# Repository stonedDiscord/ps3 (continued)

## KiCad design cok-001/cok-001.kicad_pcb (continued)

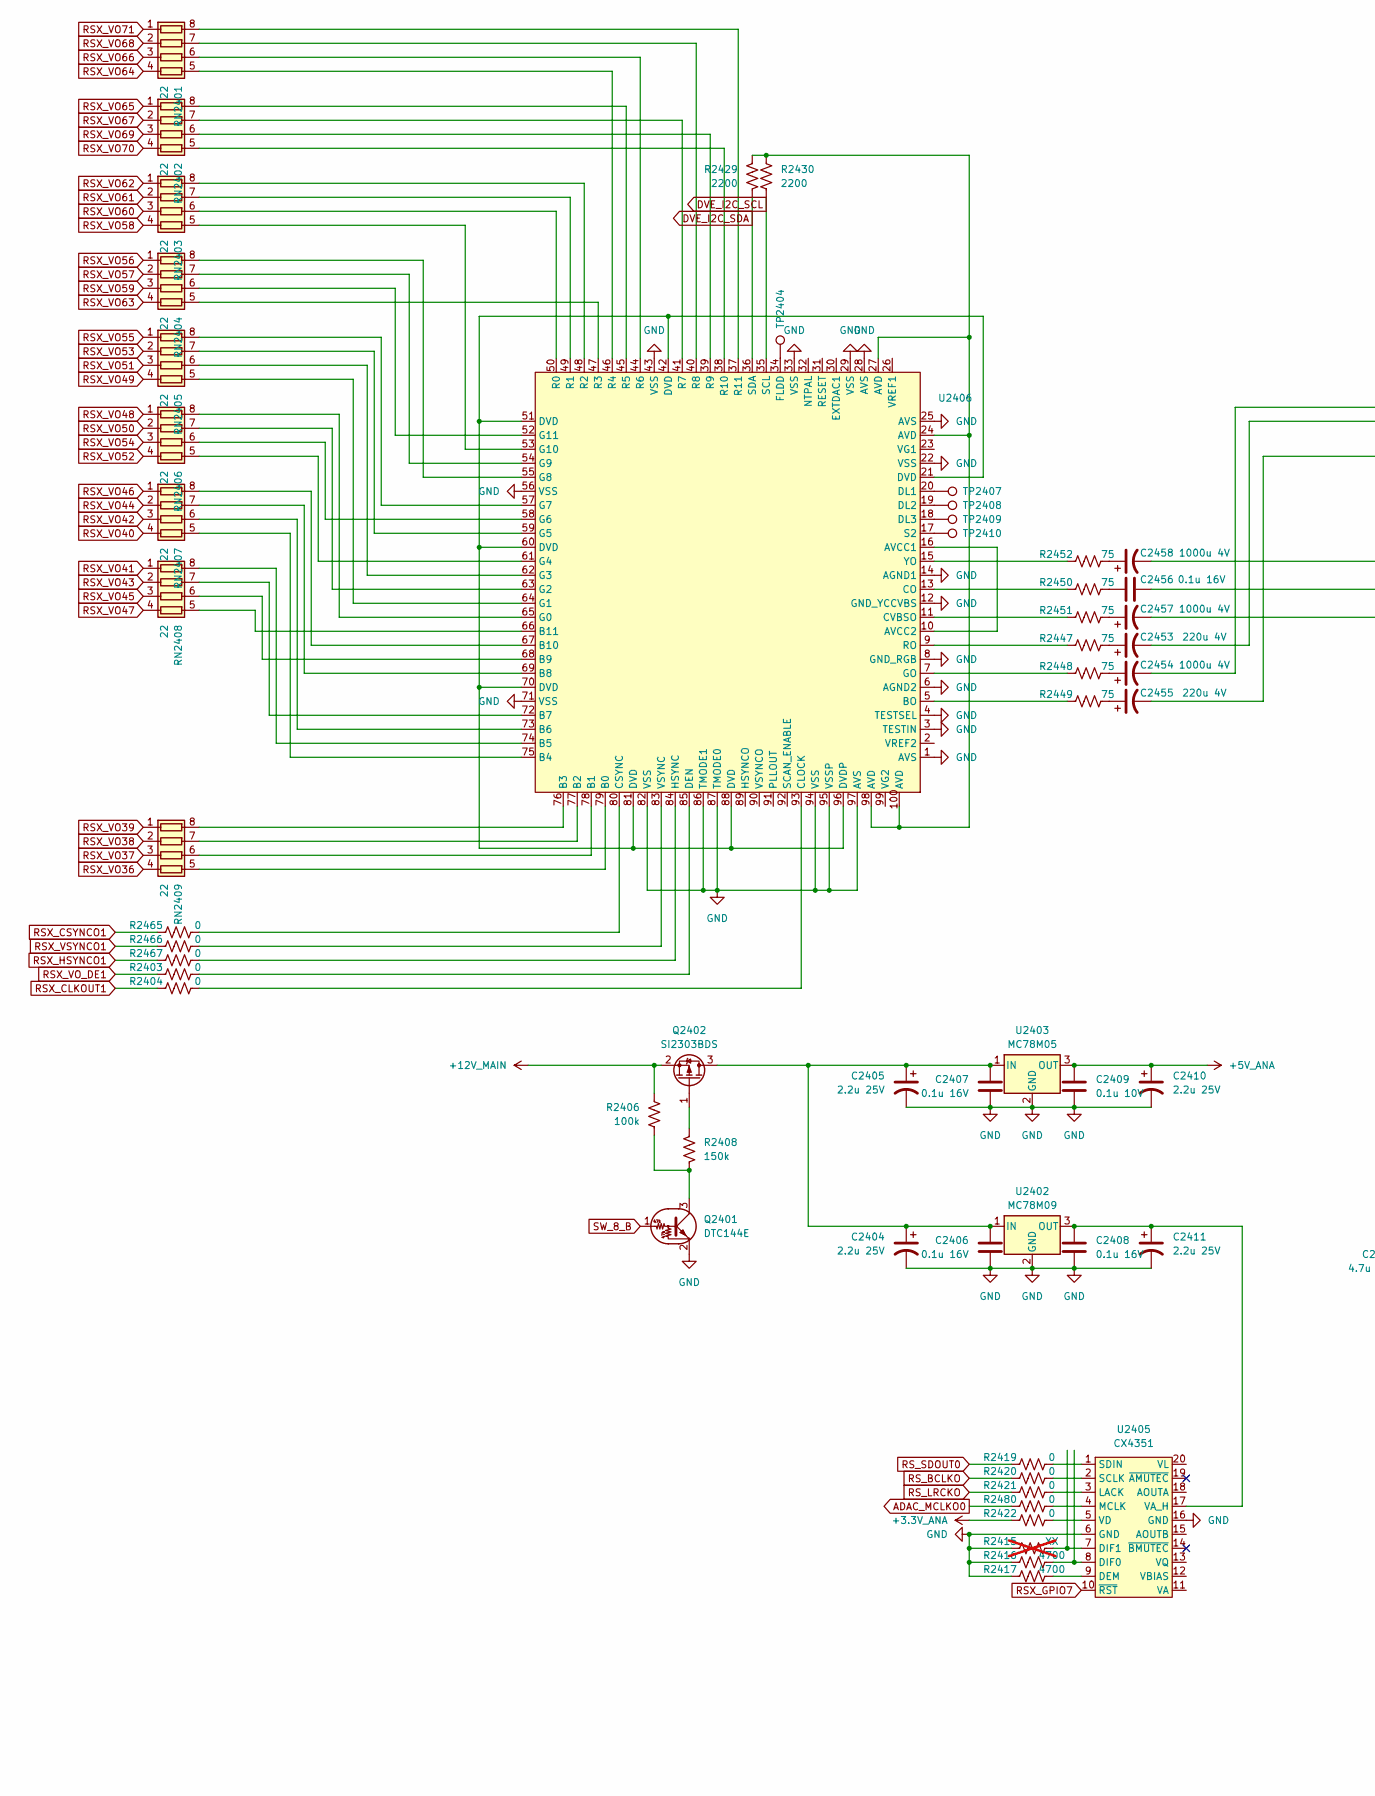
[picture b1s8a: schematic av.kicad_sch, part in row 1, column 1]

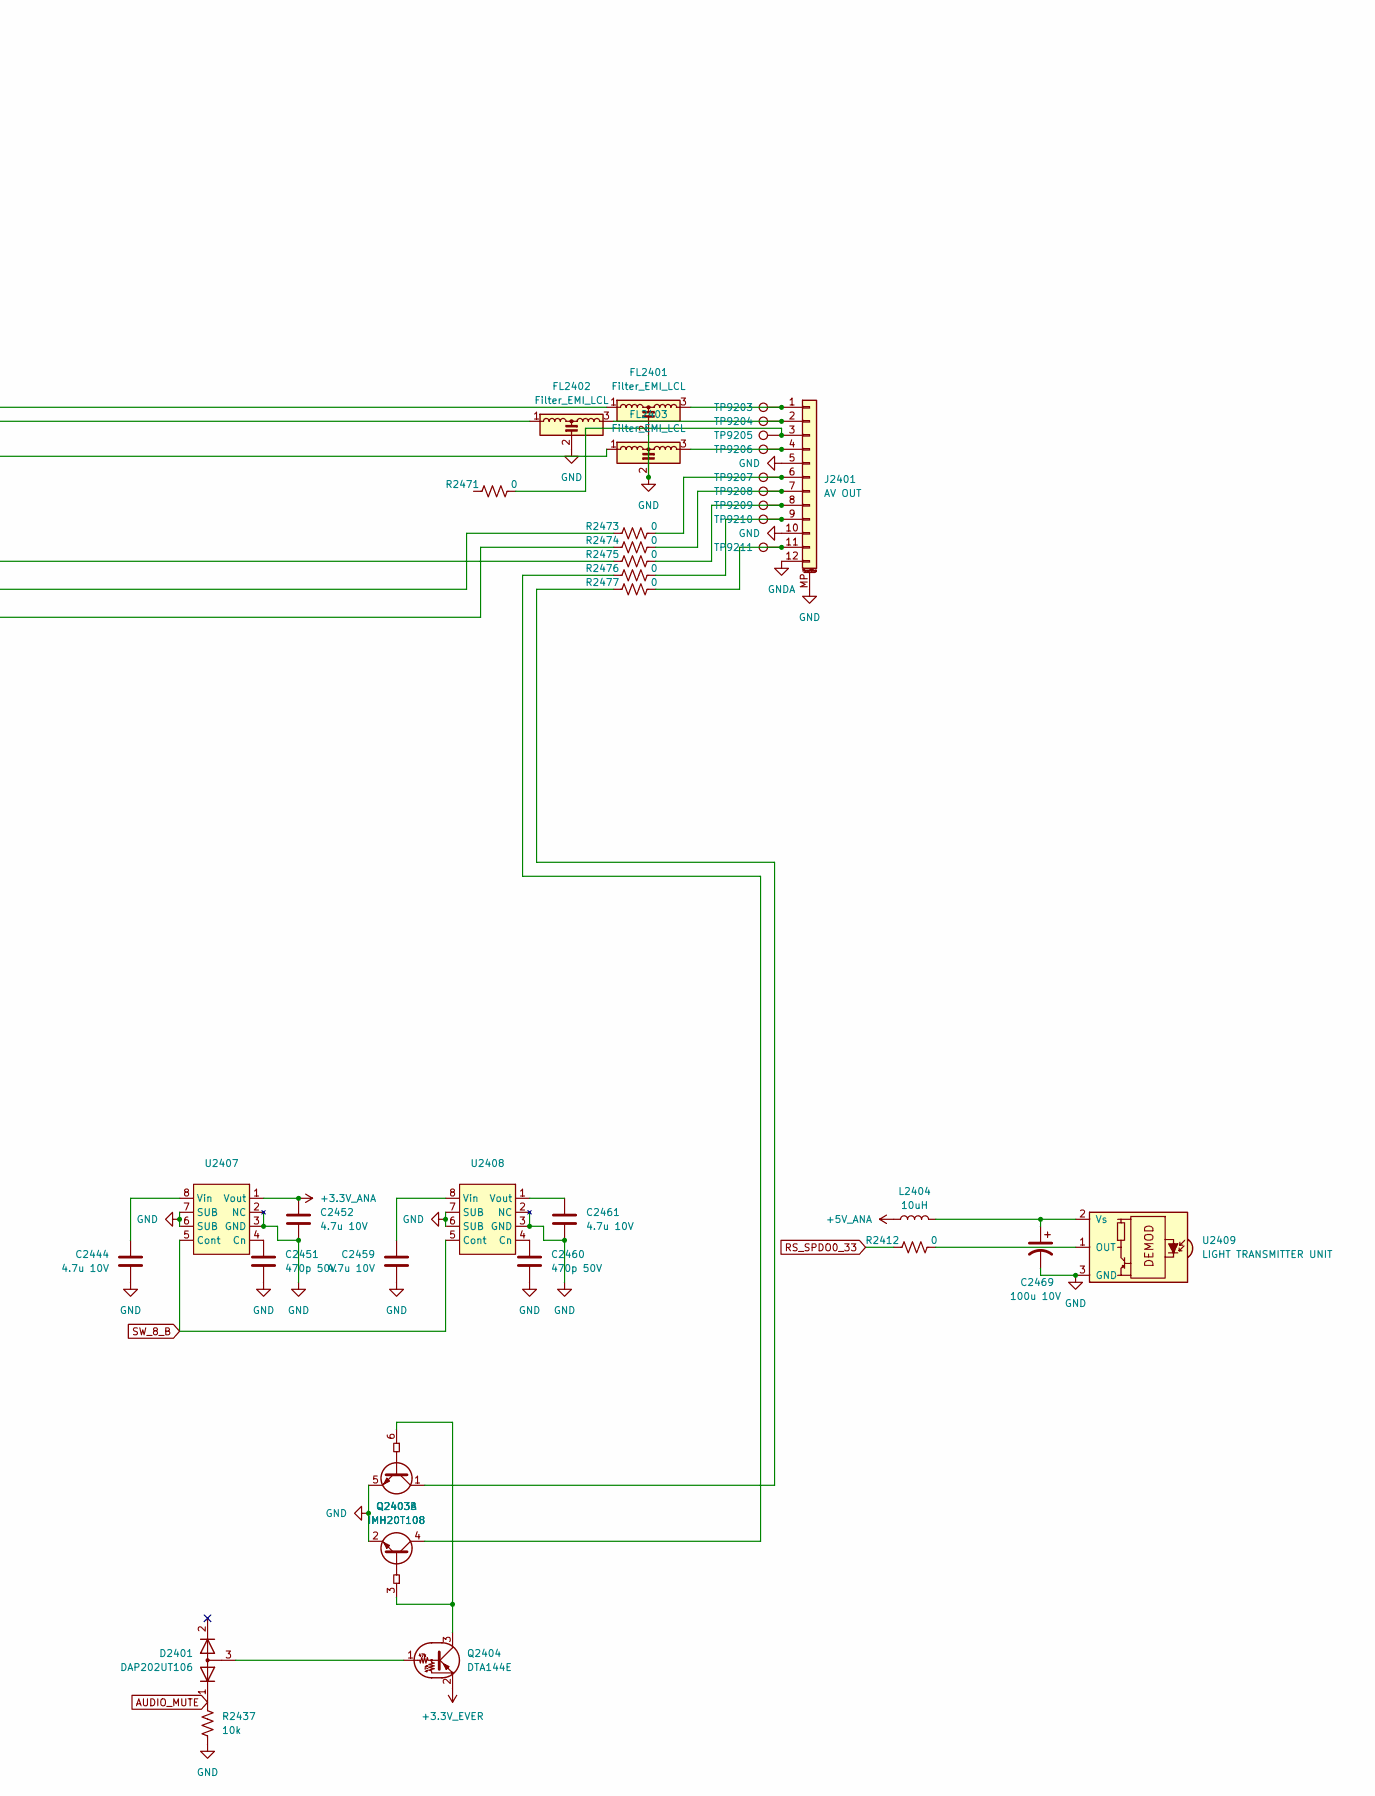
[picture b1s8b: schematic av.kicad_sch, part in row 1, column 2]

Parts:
C2404, C2405, C2411: 2.2u 25V; CP_EIA-3216-10_Kemet-I
C2406, C2407, C2408, C2456: 0.1u 16V; C_0603_1608Metric
C2409: 0.1u 10V; C_0402_1005Metric
C2410: 2.2u 25V; CP_EIA-3528-12_Kemet-T
C2444, C2452, C2459, C2461: 4.7u 10V; C_0805_2012Metric
C2451, C2460: 470p 50V; C_0402_1005Metric
C2453, C2455: 220u 4V; CP_Elec_6.3x4.5
C2454, C2457, C2458: 1000u 4V; CP_Elec_8x6.9
C2469: 100u 10V; CP_Elec_6.3x5.4
D2401: DAP202UT106; SOT-323_SC-70
FL2401, FL2402, FL2403: Filter_EMI_LCL; FL_0805_2012Metric
J2401: AV OUT; AVOUT
L2404: 10uH
Q2401: DTC144E; SOT-323_SC-70
Q2402: SI2303BDS; SOT-23
Q2403: IMH20T108; ROHM_SOT-457_ClockwisePinNumbering
Q2404: DTA144E; SOT-323_SC-70
R2403, R2404, R2419, R2420, R2421, R2465, R2466, R2467, R2480: 0; R_0402_1005Metric
R2406: 100k; R_0402_1005Metric
R2408: 150k; R_0402_1005Metric
R2412, R2471, R2473, R2474, R2475, R2476, R2477: 0; R_0603_1608Metric
R2415: XX; R_0402_1005Metric; not fitted
R2416, R2417: 4700; R_0402_1005Metric
R2422: 0; R_0805_2012Metric
R2429, R2430: 2200; R_0402_1005Metric
R2437: 10k; R_0402_1005Metric
R2447, R2448, R2449, R2450, R2451, R2452: 75; R_0603_1608Metric
RN2401, RN2402, RN2403, RN2404, RN2405, RN2406, RN2407, RN2408, RN2409: 22; R_Array_Convex_4x0402
TP2404, TP2407, TP2408, TP2409, TP2410: TestPoint; TestPoint_Pad_1.0x1.0mm
TP9203, TP9204, TP9205, TP9206, TP9207, TP9208, TP9209, TP9210, TP9211: TestPoint; TestPoint_Pad_D1.5mm
U2402: MC78M09; TO-252-2
U2403: MC78M05; TO-252-2
U2405: CX4351; SSOP-20_4.4x6.5mm_P0.65mm
U2406: TQFP-100_14x14mm_P0.5mm
U2407, U2408: SSOP-8_3.9x5.05mm_P1.27mm
U2409: LIGHT TRANSMITTER UNIT; Vishay_MOLD-3Pin

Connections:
+3.3V_ANA: C2452.1, R2422.1, U2407.1 (Vout); also elsewhere on the board
+3.3V_EVER: Q2404.2 (E); also elsewhere on the board
+5V_ANA: C2409.1, C2410.1, L2404.1, U2403.3 (OUT)
+12V_MAIN: Q2402.2 (S), R2406.1; also elsewhere on the board
ADAC_MCLKO0: R2480.1; also elsewhere on the board
AUDIO_MUTE: D2401.1 (K), R2437.2; also elsewhere on the board
DVE_I2C_SCL: R2430.1, U2406.35 (SCL); also elsewhere on the board
DVE_I2C_SDA: R2429.1, U2406.36 (SDA); also elsewhere on the board
GND: C2404.2, C2405.2, C2406.2, C2407.2, C2408.2, C2409.2, C2410.2, C2411.2, C2444.2, C2451.2, C2452.2, C2459.2, C2460.2, C2461.2, C2469.2, FL2401.2, FL2402.2, FL2403.2, J2401.5, J2401.10, J2401.MP (MountPin), Q2401.2 (E), Q2403.2 (E2), Q2403.5 (E1), R2415.1, R2416.1, R2417.1, R2437.1, U2402.2 (GND), U2403.2 (GND), U2405.6 (GND), U2405.16 (GND), U2406.1 (AVS), U2406.3 (TESTIN), U2406.4 (TESTSEL), U2406.6 (AGND2), U2406.8 (GND_RGB), U2406.12 (GND_YCCVBS), U2406.14 (AGND1), U2406.22 (VSS), U2406.25 (AVS), U2406.28 (AVS), U2406.29 (VSS), U2406.33 (VSS), U2406.43 (VSS), U2406.56 (VSS), U2406.71 (VSS), U2406.82 (VSS), U2406.86 (TMODE1), U2406.87 (TMODE0), U2406.94 (VSS), U2406.95 (VSSP), U2406.97 (AVS), U2407.2 (NC), U2407.3 (GND), U2407.6 (SUB), U2407.7 (SUB), U2408.2 (NC), U2408.3 (GND), U2408.6 (SUB), U2408.7 (SUB), U2409.3 (GND); also elsewhere on the board
GNDA: J2401.12
unnamed: C2453.1, R2447.2
unnamed: C2453.2, FL2402.1
unnamed: C2454.1, R2448.2
unnamed: C2454.2, FL2401.1
unnamed: C2455.1, R2449.2
unnamed: C2455.2, FL2403.1
unnamed: C2456.1, R2473.1
unnamed: C2456.2, R2450.2
unnamed: C2457.1, R2451.2
unnamed: C2457.2, R2474.1
unnamed: C2458.1, R2452.2
unnamed: C2458.2, R2475.1
unnamed: D2401.3 (A), Q2404.1 (B)
unnamed: FL2401.3, J2401.1, TP9203.1 (1_1)
unnamed: FL2402.3, J2401.2, TP9204.1 (1_1)
unnamed: J2401.3, R2471.2, TP9205.1 (1_1)
unnamed: FL2403.3, J2401.4, TP9206.1 (1_1)
unnamed: J2401.6, R2473.2, TP9207.1 (1_1)
unnamed: J2401.7, R2474.2, TP9208.1 (1_1)
unnamed: J2401.8, R2475.2, TP9209.1 (1_1)
unnamed: J2401.9, R2476.2, TP9210.1 (1_1)
unnamed: J2401.11, R2477.2, TP9211.1 (1_1)
unnamed: Q2401.3 (C), R2406.2, R2408.2
unnamed: C2404.1, C2405.1, C2406.1, C2407.1, Q2402.3 (D), U2402.1 (IN), U2403.1 (IN)
unnamed: Q2402.1 (G), R2408.1
unnamed: Q2403.3 (B2), Q2403.6 (B1), Q2404.3 (C)
unnamed: Q2403.1 (C1), R2477.1
unnamed: Q2403.4 (C2), R2476.1
unnamed: R2429.2, R2430.2, U2406.24 (AVD), U2406.27 (AVD), U2406.98 (AVD), U2406.100 (AVD)
unnamed: RN2401.8 (R1.2), U2406.37 (R11)
unnamed: RN2401.7 (R2.2), U2406.40 (R8)
unnamed: RN2401.6 (R3.2), U2406.44 (R6)
unnamed: RN2401.5 (R4.2), U2406.46 (R4)
unnamed: RN2402.8 (R1.2), U2406.45 (R5)
unnamed: RN2402.7 (R2.2), U2406.41 (R7)
unnamed: RN2402.6 (R3.2), U2406.39 (R9)
unnamed: RN2402.5 (R4.2), U2406.38 (R10)
unnamed: RN2403.8 (R1.2), U2406.48 (R2)
unnamed: RN2403.7 (R2.2), U2406.49 (R1)
unnamed: RN2403.6 (R3.2), U2406.50 (R0)
unnamed: RN2403.5 (R4.2), U2406.53 (G10)
unnamed: RN2404.8 (R1.2), U2406.55 (G8)
unnamed: RN2404.7 (R2.2), U2406.54 (G9)
unnamed: RN2404.6 (R3.2), U2406.52 (G11)
unnamed: RN2404.5 (R4.2), U2406.47 (R3)
unnamed: RN2405.8 (R1.2), U2406.57 (G7)
unnamed: RN2405.7 (R2.2), U2406.59 (G5)
unnamed: RN2405.6 (R3.2), U2406.62 (G3)
unnamed: RN2405.5 (R4.2), U2406.64 (G1)
unnamed: RN2406.8 (R1.2), U2406.65 (G0)
unnamed: RN2406.7 (R2.2), U2406.63 (G2)
unnamed: RN2406.6 (R3.2), U2406.58 (G6)
unnamed: RN2406.5 (R4.2), U2406.61 (G4)
unnamed: RN2407.8 (R1.2), U2406.67 (B10)
unnamed: RN2407.7 (R2.2), U2406.69 (B8)
unnamed: RN2407.6 (R3.2), U2406.73 (B6)
unnamed: RN2407.5 (R4.2), U2406.75 (B4)
unnamed: RN2408.8 (R1.2), U2406.74 (B5)
unnamed: RN2408.7 (R2.2), U2406.72 (B7)
unnamed: RN2408.6 (R3.2), U2406.68 (B9)
unnamed: RN2408.5 (R4.2), U2406.66 (B11)
unnamed: RN2409.8 (R1.2), U2406.76 (B3)
unnamed: RN2409.7 (R2.2), U2406.77 (B2)
unnamed: RN2409.6 (R3.2), U2406.78 (B1)
unnamed: RN2409.5 (R4.2), U2406.79 (B0)
unnamed: C2408.1, C2411.1, U2402.3 (OUT), U2405.17 (VA_H)
unnamed: R2417.2, U2405.9 (DEM)
unnamed: R2416.2, U2405.8 (DIF0)
unnamed: R2415.2, U2405.7 (DIF1)
unnamed: R2421.2, U2405.3 (LACK)
unnamed: R2480.2, U2405.4 (MCLK)
unnamed: R2420.2, U2405.2 (SCLK)
unnamed: R2419.2, U2405.1 (SDIN)
unnamed: R2422.2, U2405.5 (VD)
unnamed: U2406.10 (AVCC2), U2406.16 (AVCC1)
unnamed: R2449.1, U2406.5 (BO)
unnamed: R2404.2, U2406.93 (CLOCK)
unnamed: R2450.1, U2406.13 (CO)
unnamed: R2465.2, U2406.80 (CSYNC)
unnamed: R2451.1, U2406.11 (CVBSO)
unnamed: R2403.2, U2406.85 (DEN)
unnamed: TP2407.1 (1_1), U2406.20 (DL1)
unnamed: TP2408.1 (1_1), U2406.19 (DL2)
unnamed: TP2409.1 (1_1), U2406.18 (DL3)
unnamed: U2406.21 (DVD), U2406.42 (DVD), U2406.51 (DVD), U2406.60 (DVD), U2406.70 (DVD), U2406.81 (DVD), U2406.88 (DVD), U2406.96 (DVDP)
unnamed: TP2404.1 (1_1), U2406.34 (FLDD)
unnamed: R2448.1, U2406.7 (GO)
unnamed: R2467.2, U2406.84 (HSYNC)
unnamed: R2447.1, U2406.9 (RO)
unnamed: TP2410.1 (1_1), U2406.17 (S2)
unnamed: R2466.2, U2406.83 (VSYNC)
unnamed: R2452.1, U2406.15 (YO)
unnamed: C2451.1, U2407.4 (Cn)
unnamed: C2444.1, U2407.8 (Vin)
unnamed: C2460.1, U2408.4 (Cn)
unnamed: C2459.1, U2408.8 (Vin)
unnamed: C2461.1, U2408.1 (Vout)
unnamed: R2412.2, U2409.1 (OUT)
unnamed: C2469.1, L2404.2, U2409.2 (Vs)
RSX_CLKOUT1: R2404.1
RSX_CSYNCO1: R2465.1
RSX_GPIO7: U2405.10 (~RST); also elsewhere on the board
RSX_HSYNCO1: R2467.1
RSX_VO36: RN2409.4 (R4.1); also elsewhere on the board
RSX_VO37: RN2409.3 (R3.1)
RSX_VO38: RN2409.2 (R2.1); also elsewhere on the board
RSX_VO39: RN2409.1 (R1.1); also elsewhere on the board
RSX_VO40: RN2407.4 (R4.1)
RSX_VO41: RN2408.1 (R1.1); also elsewhere on the board
RSX_VO42: RN2407.3 (R3.1); also elsewhere on the board
RSX_VO43: RN2408.2 (R2.1); also elsewhere on the board
RSX_VO44: RN2407.2 (R2.1); also elsewhere on the board
RSX_VO45: RN2408.3 (R3.1); also elsewhere on the board
RSX_VO46: RN2407.1 (R1.1); also elsewhere on the board
RSX_VO47: RN2408.4 (R4.1); also elsewhere on the board
RSX_VO48: RN2406.1 (R1.1); also elsewhere on the board
RSX_VO49: RN2405.4 (R4.1); also elsewhere on the board
RSX_VO50: RN2406.2 (R2.1); also elsewhere on the board
RSX_VO51: RN2405.3 (R3.1); also elsewhere on the board
RSX_VO52: RN2406.4 (R4.1); also elsewhere on the board
RSX_VO53: RN2405.2 (R2.1); also elsewhere on the board
RSX_VO54: RN2406.3 (R3.1); also elsewhere on the board
RSX_VO55: RN2405.1 (R1.1); also elsewhere on the board
RSX_VO56: RN2404.1 (R1.1); also elsewhere on the board
RSX_VO57: RN2404.2 (R2.1); also elsewhere on the board
RSX_VO58: RN2403.4 (R4.1); also elsewhere on the board
RSX_VO59: RN2404.3 (R3.1); also elsewhere on the board
RSX_VO60: RN2403.3 (R3.1); also elsewhere on the board
RSX_VO61: RN2403.2 (R2.1); also elsewhere on the board
RSX_VO62: RN2403.1 (R1.1); also elsewhere on the board
RSX_VO63: RN2404.4 (R4.1); also elsewhere on the board
RSX_VO64: RN2401.4 (R4.1); also elsewhere on the board
RSX_VO65: RN2402.1 (R1.1); also elsewhere on the board
RSX_VO66: RN2401.3 (R3.1); also elsewhere on the board
RSX_VO67: RN2402.2 (R2.1); also elsewhere on the board
RSX_VO68: RN2401.2 (R2.1); also elsewhere on the board
RSX_VO69: RN2402.3 (R3.1); also elsewhere on the board
RSX_VO70: RN2402.4 (R4.1); also elsewhere on the board
RSX_VO71: RN2401.1 (R1.1); also elsewhere on the board
RSX_VO_DE1: R2403.1; also elsewhere on the board
RSX_VSYNCO1: R2466.1
RS_BCLKO: R2420.1; also elsewhere on the board
RS_LRCKO: R2421.1; also elsewhere on the board
RS_SDOUT0: R2419.1; also elsewhere on the board
RS_SPDO0_33: R2412.1; also elsewhere on the board
SW_8_B: Q2401.1 (B), U2407.5 (Cont), U2408.5 (Cont); also elsewhere on the board

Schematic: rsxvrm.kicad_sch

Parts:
C6205: 1u 10V; C_0402_1005Metric
C6207: 0.022u 16V; C_0402_1005Metric
C6211: 0.1u 10V; C_0402_1005Metric
C6212: 22u 2.5V; C_0402_1005Metric
FL6229, FL6230, FL6231, FL6232: 1200u; Proadlizer
L6201, L6202: 0.3uH; L_Bourns_SRR1208_12.7x12.7mm
Q6200: SI4866DY; SSOP-8_3.9x5.05mm_P1.27mm
R6200, R6201, R6202, R6203, R6204, R6206, R6208, R6209: 1500; R_0402_1005Metric
R6211: 220; R_0402_1005Metric
R6214, R6216: XX; R_0402_1005Metric; not fitted
R6219, R6222: 0; R_0402_1005Metric
R6228, R6233: 560; R_0402_1005Metric
R6248, R6249: 0.001; R_2512_6332Metric
TP9651: TestPoint; TestPoint_Pad_D1.5mm
U6200: BD3520FVM-TR; MSOP-8_2.9x4mm_P0.65mm
U6201: NCP5318FTR2G; LQFP-32_7x7mm_P0.8mm
U6202, U6203: iP2003APbF
U6204: TC7SG08FU; Texas_R-PDSO-N5_DRL-5

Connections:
+1.2V_RSX_VDDA: C6211.1, C6212.1, Q6200.5 (D), Q6200.6 (D), Q6200.7 (D), Q6200.8 (D), R6222.2, TP9651.1 (1_1), U6200.6 (VS)
+1.2V_RSX_VDDC: FL6229.3, FL6230.3, FL6231.3, FL6232.3
+1.7V_MISC: Q6200.1 (S), Q6200.2 (S), Q6200.3 (S), R6219.2; also elsewhere on the board
+3.3V_MISC: R6200.1, R6201.1, R6202.1, R6203.1, R6204.1, R6206.1, R6208.1, R6209.1, U6204.5 (VCC); also elsewhere on the board
+5V_MISC: C6205.1, U6200.4 (VCC); also elsewhere on the board
GND: C6205.2, C6207.2, C6211.2, C6212.2, FL6229.2, FL6230.2, FL6231.2, FL6232.2, R6214.1, R6216.1, U6200.2 (GND), U6201.15 (CS3N), U6201.16 (CS3P), U6201.17 (GND), U6201.25 (CS1P), U6201.26 (CS1N), U6202.5 (PGND), U6202.7 (PGND), U6203.5 (PGND), U6203.7 (PGND), U6204.3 (GND); also elsewhere on the board
unnamed: C6207.1, R6211.1
unnamed: L6201.2, R6228.2, R6248.1
unnamed: L6202.2, R6233.2, R6249.1
unnamed: Q6200.4 (G), R6211.2, U6200.7 (G)
unnamed: R6214.2, R6219.1, U6200.8 (VD)
unnamed: R6216.2, R6222.1, U6200.5 (VFB)
unnamed: FL6229.1, FL6230.1, FL6231.1, FL6232.1, R6248.2, R6249.2, U6201.13 (CS4N), U6201.28 (CS2N)
unnamed: R6228.1, U6201.27 (CS2P)
unnamed: R6233.1, U6201.14 (CS4P)
unnamed: U6201.8 (DRVON), U6204.2
unnamed: U6201.20 (GATE2), U6202.3 (PWM)
unnamed: U6201.18 (GATE4), U6203.3 (PWM)
unnamed: U6202.2 (ENABLE), U6203.2 (ENABLE), U6204.4
unnamed: L6201.1, U6202.6 (Vsw)
unnamed: U6202.9 (Vsws1), U6202.10 (Vsws2)
unnamed: L6202.1, U6203.6 (Vsw)
unnamed: U6203.9 (Vsws1), U6203.10 (Vsws2)
RSXVRM_VID0: R6208.2, U6201.31 (Vid0)
RSXVRM_VID1: R6206.2, U6201.32 (Vid1)
RSXVRM_VID2: R6204.2, U6201.1 (Vid2)
RSXVRM_VID3: R6203.2, U6201.2 (Vid3)
RSXVRM_VID4: R6202.2, U6201.3 (Vid4)
RSXVRM_VID5: R6200.2, U6201.30 (Vid5)
SW_5_A: R6209.2, U6201.29 (ENABLE), U6204.1; also elsewhere on the board
SW_5_B: U6200.3 (EN)
~RSX_POW_FAIL: R6201.2, U6201.7 (PWRGD); also elsewhere on the board

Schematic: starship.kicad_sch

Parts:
C3823, C3824, C3825, C3826: 0.1u; C_0402_1005Metric
R3801, R3807, R3808, R3830, R3831, R3832, R3833, R3834, R3835, R3836, R3837: 10k; R_0402_1005Metric
R3802: 22; R_0402_1005Metric
R3812, R3814: 0; R_0402_1005Metric; not fitted
R3813, R3815, R3821, R3823, R3838, R3839, R3842, R3843, R3844: 0; R_0402_1005Metric
R3840, R3841: 2200; R_0402_1005Metric
TP9303, TP9304, TP9305, TP9306, TP9307, TP9308, TP9309, TP9310, TP9321, TP9322, TP9323, TP9324, TP9325, TP9326, TP9327, TP9328, TP9329, TP9330, TP9331, TP9332, TP9333, TP9334, TP9335, TP9336, TP9337, TP9338, TP9339, TP9340, TP9341, TP9342, TP9343, TP9344, TP9345, TP9346, TP9347, TP9348, TP9349, TP9350, TP9351, TP9352, TP9353, TP9354: TestPoint; TestPoint_Pad_D1.5mm
U3801: Starship2
U3802, U3803: K9F1G08U0A; TSOP-I-48_18.4x12mm_P0.5mm

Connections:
+3V3SB: R3801.2, R3807.2, R3808.2, U3801.A10 (VDD33), U3801.B14 (VDD33), U3801.D5 (VDD33), U3801.D6 (VDD33), U3801.D9 (VDD33), U3801.D10 (VDD33), U3801.G12 (VDD33), U3801.H11 (VDD33), U3801.K11 (VDD33)
/Starship2/SS2_FALE0: U3801.L9 (FALE0), U3802.17 (ALE)
/Starship2/SS2_FALE1: U3801.L5 (FALE1), U3803.17 (ALE)
/Starship2/SS2_FCLE0: U3801.M9 (FCLE0), U3802.16 (CLE)
/Starship2/SS2_FCLE1: U3801.M4 (FCLE1), U3803.16 (CLE)
/Starship2/SS2_FD0_0: U3801.M14 (FD00), U3802.29 (I/O0)
/Starship2/SS2_FD0_1: U3801.M13 (FD01), U3802.30 (I/O1)
/Starship2/SS2_FD0_2: U3801.N13 (FD02), U3802.31 (I/O2)
/Starship2/SS2_FD0_3: U3801.P13 (FD03), U3802.32 (I/O3)
/Starship2/SS2_FD0_4: U3801.P12 (FD04), U3802.41 (I/O4)
/Starship2/SS2_FD0_5: U3801.P11 (FD05), U3802.42 (I/O5)
/Starship2/SS2_FD0_6: U3801.P10 (FD06), U3802.43 (I/O6)
/Starship2/SS2_FD0_7: U3801.P9 (FD07), U3802.44 (I/O7)
/Starship2/SS2_FD1_0: U3801.P7 (FD10), U3803.29 (I/O0)
/Starship2/SS2_FD1_1: U3801.P6 (FD11), U3803.30 (I/O1)
/Starship2/SS2_FD1_2: U3801.P5 (FD12), U3803.31 (I/O2)
/Starship2/SS2_FD1_3: U3801.P4 (FD13), U3803.32 (I/O3)
/Starship2/SS2_FD1_4: U3801.P3 (FD14), U3803.41 (I/O4)
/Starship2/SS2_FD1_5: U3801.P2 (FD15), U3803.42 (I/O5)
/Starship2/SS2_FD1_6: U3801.P1 (FD16), U3803.43 (I/O6)
/Starship2/SS2_FD1_7: U3801.M2 (FD17), U3803.44 (I/O7)
/Starship2/SS2_XFCE0: U3801.M8 (XFCE0), U3802.9 (~CE)
/Starship2/SS2_XFCE1: U3801.L3 (XFCE1), U3803.9 (~CE)
/Starship2/SS2_XFRB0: R3841.1, U3801.M7 (XFRB0), U3802.7 (R/~B)
/Starship2/SS2_XFRB1: R3840.1, U3801.L2 (XFRB1), U3803.7 (R/~B)
/Starship2/SS2_XFRE0: U3801.P8 (XFRE0), U3802.8 (~RE)
/Starship2/SS2_XFRE1: U3801.M3 (XFRE1), U3803.8 (~RE)
/Starship2/SS2_XFWE0: U3801.M10 (XFWE0), U3802.18 (~WE)
/Starship2/SS2_XFWE1: U3801.M5 (XFWE1), U3803.18 (~WE)
/Starship2/SS2_XFWP0: R3812.2, U3801.M11 (XFWP0)
/Starship2/SS2_XFWP1: R3814.1, U3801.M6 (XFWP1)
GND: C3823.2, C3824.2, C3825.2, C3826.2, R3830.2, R3831.2, R3832.2, R3833.2, R3834.2, R3835.2, R3836.2, R3837.2, R3843.1, U3801.D4 (GND), U3801.D11 (GND), U3801.F6 (GND), U3801.F7 (GND), U3801.F8 (GND), U3801.F9 (GND), U3801.G6 (GND), U3801.G7 (GND), U3801.G8 (GND), U3801.G9 (GND), U3801.H2 (GNDP), U3801.H6 (GND), U3801.H7 (GND), U3801.H8 (GND), U3801.H9 (GND), U3801.J6 (GND), U3801.J7 (GND), U3801.J8 (GND), U3801.J9 (GND), U3801.L4 (GND), U3801.L11 (GND), U3802.13 (Vss), U3802.36 (Vss), U3803.13 (Vss), U3803.36 (Vss); also elsewhere on the board
unnamed: C3823.1, C3824.1, C3825.1, C3826.1, R3813.2, R3815.2, R3840.2, R3841.2, U3802.12 (Vcc), U3802.37 (Vcc), U3803.12 (Vcc), U3803.37 (Vcc)
unnamed: R3821.1, R3823.1, R3842.1, R3844.1, U3801.E1 (VDD33), U3801.H4 (VDD33), U3801.J2 (VDD33)
unnamed: R3802.2, U3801.D1 (BRDY)
unnamed: R3843.2, U3801.H3 (CLKSEL)
unnamed: R3830.1, U3801.D13 (ID0)
unnamed: R3831.1, U3801.D14 (ID1)
unnamed: R3832.1, U3801.E13 (ID2)
unnamed: R3833.1, U3801.E14 (ID3)
unnamed: R3834.1, U3801.F13 (ID4)
unnamed: R3835.1, U3801.F14 (ID5)
unnamed: R3836.1, U3801.G13 (ID6)
unnamed: R3837.1, U3801.G14 (ID7)
unnamed: R3844.2, U3801.J4 (PLLEN)
unnamed: R3821.2, U3801.F3 (PLLSEL1)
unnamed: R3823.2, U3801.F2 (PLLSEL3)
unnamed: R3801.1, R3838.2, R3839.2, U3801.B6 (XHRST)
unnamed: R3842.2, U3801.K1 (XIN)
unnamed: U3802.3 (DNU), U3802.10 (DNU), U3802.15 (DNU), U3802.22 (DNU), U3802.27 (DNU), U3802.34 (DNU), U3802.39 (DNU), U3802.46 (DNU)
unnamed: R3812.1, R3813.1, U3802.19 (~WP)
unnamed: U3803.3 (DNU), U3803.10 (DNU), U3803.15 (DNU), U3803.22 (DNU), U3803.27 (DNU), U3803.34 (DNU), U3803.39 (DNU), U3803.46 (DNU)
unnamed: R3814.2, R3815.1, U3803.19 (~WP)
SB_EBUS_ADDR0: TP9338.1 (1_1), U3801.A1 (HA0); also elsewhere on the board
SB_EBUS_ADDR1: TP9337.1 (1_1), U3801.B2 (HA1); also elsewhere on the board
SB_EBUS_ADDR2: TP9336.1 (1_1), U3801.A3 (HA2); also elsewhere on the board
SB_EBUS_ADDR3: TP9335.1 (1_1), U3801.B3 (HA3); also elsewhere on the board
SB_EBUS_ADDR4: TP9334.1 (1_1), U3801.A4 (HA4); also elsewhere on the board
SB_EBUS_ADDR5: TP9333.1 (1_1), U3801.B4 (HA5); also elsewhere on the board
SB_EBUS_ADDR6: TP9332.1 (1_1), U3801.A5 (HA6); also elsewhere on the board
SB_EBUS_ADDR7: TP9331.1 (1_1), U3801.B5 (HA7); also elsewhere on the board
SB_EBUS_ADDR8: TP9330.1 (1_1), U3801.B7 (HA8); also elsewhere on the board
SB_EBUS_ADDR9: TP9329.1 (1_1), U3801.A8 (HA9); also elsewhere on the board
SB_EBUS_ADDR10: TP9328.1 (1_1), U3801.B8 (HA10); also elsewhere on the board
SB_EBUS_ADDR11: TP9327.1 (1_1), U3801.A9 (HA11); also elsewhere on the board
SB_EBUS_ADDR12: TP9326.1 (1_1), U3801.B9 (HA12); also elsewhere on the board
SB_EBUS_ADDR13: TP9325.1 (1_1), U3801.B10 (HA13); also elsewhere on the board
SB_EBUS_ADDR14: TP9324.1 (1_1), U3801.A11 (HA14); also elsewhere on the board
SB_EBUS_ADDR15: TP9323.1 (1_1), U3801.B11 (HA15); also elsewhere on the board
SB_EBUS_ADDR16: TP9322.1 (1_1), U3801.A12 (HA16); also elsewhere on the board
SB_EBUS_ADDR17: TP9321.1 (1_1), U3801.A6 (HA17); also elsewhere on the board
SB_EBUS_DATA0: TP9354.1 (1_1), U3801.F4 (HD0); also elsewhere on the board
SB_EBUS_DATA1: TP9353.1 (1_1), U3801.E3 (HD1); also elsewhere on the board
SB_EBUS_DATA2: TP9352.1 (1_1), U3801.C3 (HD2); also elsewhere on the board
SB_EBUS_DATA3: TP9351.1 (1_1), U3801.C4 (HD3); also elsewhere on the board
SB_EBUS_DATA4: TP9350.1 (1_1), U3801.C6 (HD4); also elsewhere on the board
SB_EBUS_DATA5: TP9349.1 (1_1), U3801.C7 (HD5); also elsewhere on the board
SB_EBUS_DATA6: TP9348.1 (1_1), U3801.C8 (HD6); also elsewhere on the board
SB_EBUS_DATA7: TP9347.1 (1_1), U3801.C10 (HD7); also elsewhere on the board
SB_EBUS_DATA8: TP9346.1 (1_1), U3801.E2 (HD8); also elsewhere on the board
SB_EBUS_DATA9: TP9345.1 (1_1), U3801.E4 (HD9); also elsewhere on the board
SB_EBUS_DATA10: TP9344.1 (1_1), U3801.D3 (HD10); also elsewhere on the board
SB_EBUS_DATA11: TP9343.1 (1_1), U3801.C5 (HD11); also elsewhere on the board
SB_EBUS_DATA12: TP9342.1 (1_1), U3801.D7 (HD12); also elsewhere on the board
SB_EBUS_DATA13: TP9341.1 (1_1), U3801.D8 (HD13); also elsewhere on the board
SB_EBUS_DATA14: TP9340.1 (1_1), U3801.C9 (HD14); also elsewhere on the board
SB_EBUS_DATA15: TP9339.1 (1_1), U3801.C11 (HD15); also elsewhere on the board
SS2_BRDY: R3802.1, R3807.1, TP9309.1 (1_1)
~SB_EBUS_ACK: TP9308.1 (1_1), U3801.C1 (HRDY); also elsewhere on the board
~SB_EBUS_CE0: TP9307.1 (1_1), U3801.B1 (XHCE0); also elsewhere on the board
~SB_EBUS_CE2: TP9306.1 (1_1), U3801.C2 (XHCE1); also elsewhere on the board
~SB_EBUS_IOR: TP9303.1 (1_1), U3801.B12 (XHBE); also elsewhere on the board
~SB_EBUS_OE: TP9305.1 (1_1), U3801.A2 (XHOE); also elsewhere on the board
~SB_EBUS_RESET: R3838.1; also elsewhere on the board
~SB_EBUS_SWE: TP9304.1 (1_1), U3801.A7 (XHWE); also elsewhere on the board
~SS2_INT: R3808.1, TP9310.1 (1_1), U3801.D2 (XINT); also elsewhere on the board
~SS2_RESET: R3839.1
